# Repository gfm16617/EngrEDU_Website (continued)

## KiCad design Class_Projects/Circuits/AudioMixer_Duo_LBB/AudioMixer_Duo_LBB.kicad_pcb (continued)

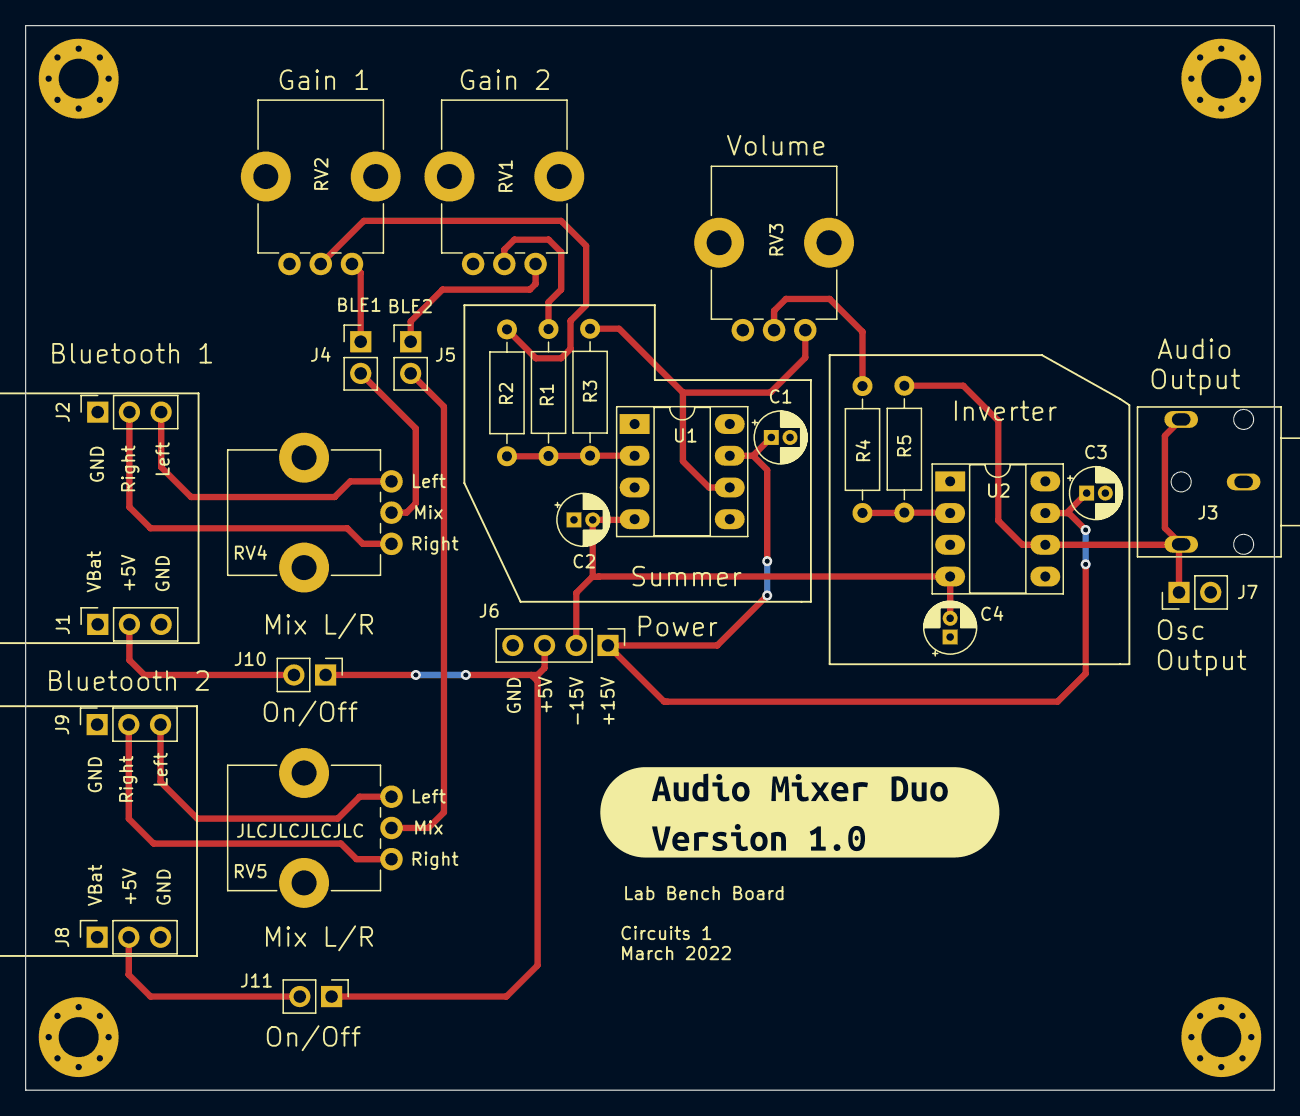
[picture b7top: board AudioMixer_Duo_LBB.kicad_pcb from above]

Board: 2 copper layers, 100.0 x 85.2 mm, 32 parts (0 on the bottom side), 21 nets.

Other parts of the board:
kibuzzard-622CD937: G***; kibuzzard-622CD937

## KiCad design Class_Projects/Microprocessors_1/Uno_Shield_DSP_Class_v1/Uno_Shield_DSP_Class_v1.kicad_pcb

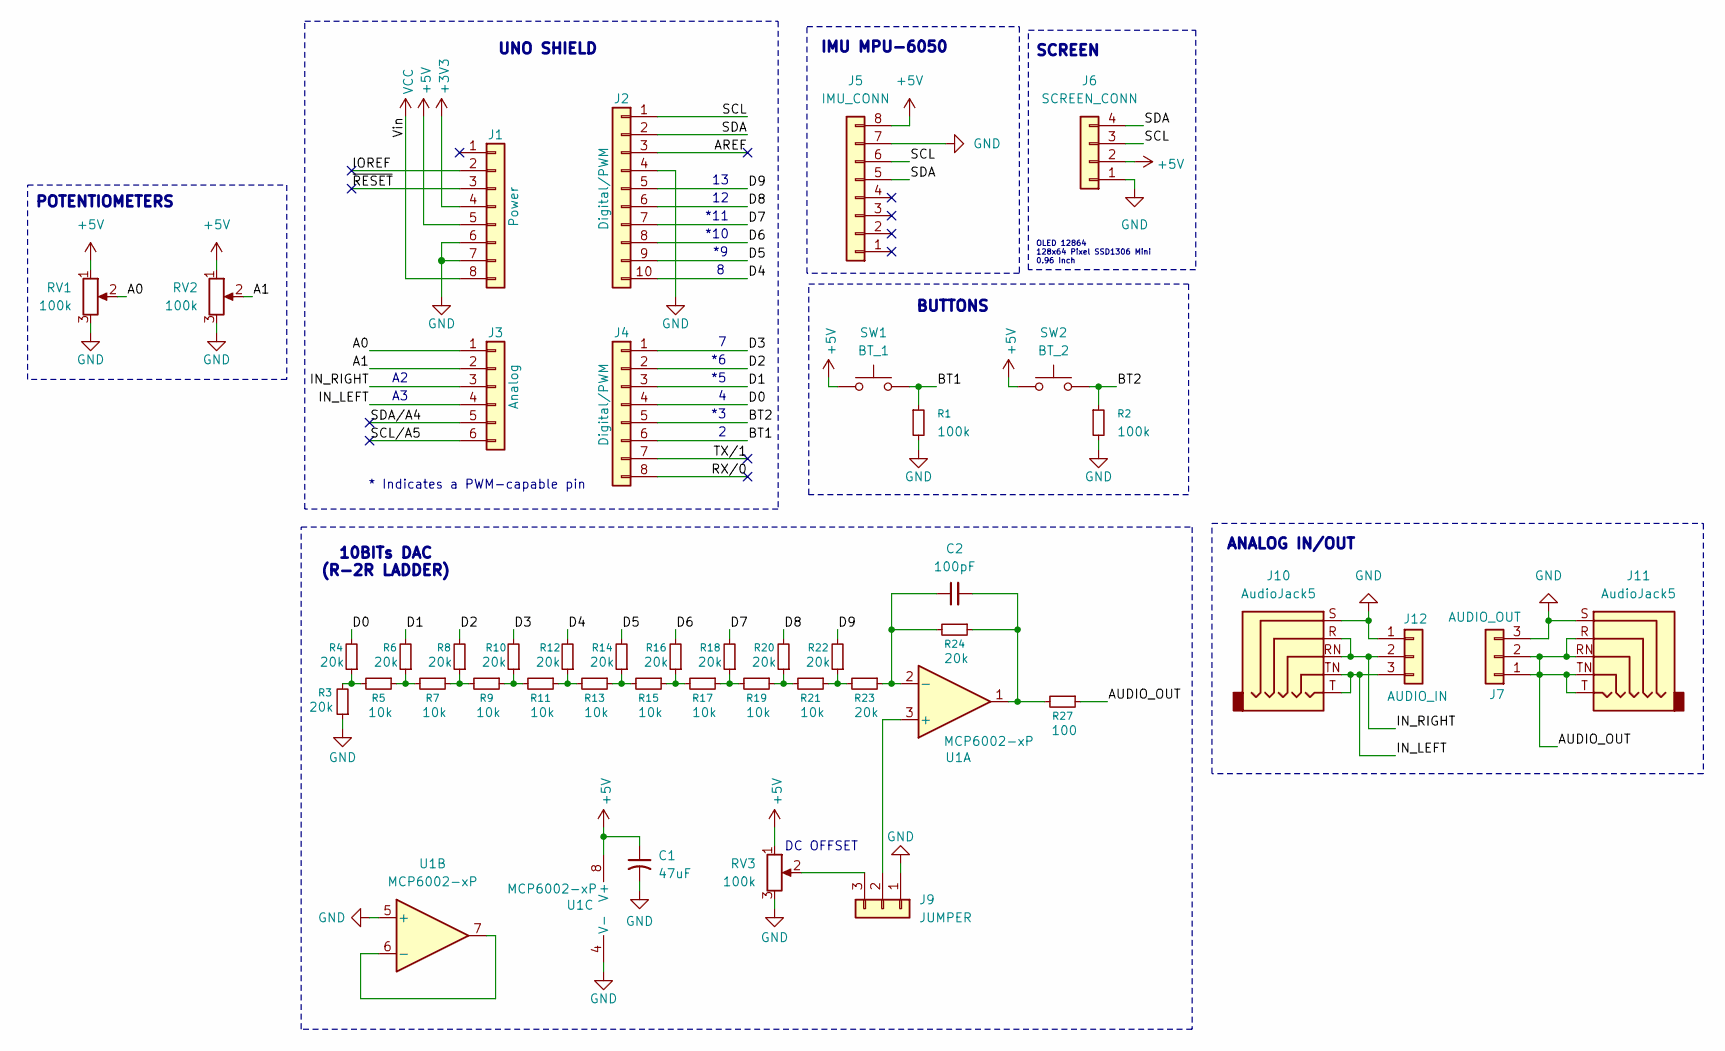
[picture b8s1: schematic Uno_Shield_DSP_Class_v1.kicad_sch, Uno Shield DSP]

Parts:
C1: 47uF; CP_Radial_D6.3mm_P2.50mm
C2: 100pF; C_Disc_D5.0mm_W2.5mm_P2.50mm
J1: Power; PinSocket_1x08_P2.54mm_Vertical
J2: Digital/PWM; PinSocket_1x10_P2.54mm_Vertical
J3: Analog; PinSocket_1x06_P2.54mm_Vertical
J4: Digital/PWM; PinSocket_1x08_P2.54mm_Vertical
J5: IMU_CONN; PinSocket_1x08_P2.54mm_Vertical
J6: SCREEN_CONN; PinHeader_1x04_P2.54mm_Vertical
J7: AUDIO_OUT; PinHeader_1x03_P2.54mm_Vertical
J9: JUMPER; PinHeader_1x03_P2.54mm_Vertical
J10, J11: AudioJack5; Jack_3.5mm_CUI_SJ1-3525N_Horizontal
J12: AUDIO_IN; PinHeader_1x03_P2.54mm_Vertical
R1, R2: 100k; R_Axial_DIN0309_L9.0mm_D3.2mm_P2.54mm_Vertical
R3, R4, R6, R8, R10, R12, R14, R16, R18, R20, R22, R23, R24: 20k; R_Axial_DIN0309_L9.0mm_D3.2mm_P2.54mm_Vertical
R5, R7, R9, R11, R13, R15, R17, R19, R21: 10k; R_Axial_DIN0309_L9.0mm_D3.2mm_P2.54mm_Vertical
R27: 100; R_Axial_DIN0309_L9.0mm_D3.2mm_P2.54mm_Vertical
RV1, RV2, RV3: 100k; Potentiometer_Bourns_3386P_Vertical
SW1: BT_1; SW_PUSH_6mm
SW2: BT_2; SW_PUSH_6mm
U1: MCP6002-xP; DIP-8_W7.62mm_Socket_LongPads

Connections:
+3V3: J1.4
+5V: C1.1, J1.5, J5.8, J6.2, RV1.1, RV2.1, RV3.1, SW1.1, SW2.1, U1.8 (V+)
/A0: J3.1, RV1.2
/A1: J3.2, RV2.2
/AREF: J2.3
/AUDIO_OUT: J7.1, J7.2, J11.R, J11.RN, J11.T, J11.TN, R27.1
/BT1: J4.6, R1.1, SW1.2
/BT2: J4.5, R2.1, SW2.2
/D0: J4.4, R4.2
/D1: J4.3, R6.2
/D2: J4.2, R8.2
/D3: J4.1, R10.2
/D4: J2.10, R12.2
/D5: J2.9, R14.2
/D6: J2.8, R16.2
/D7: J2.7, R18.2
/D8: J2.6, R20.2
/D9: J2.5, R22.2
/IN_LEFT: J3.4, J10.T, J10.TN, J12.3
/IN_RIGHT: J3.3, J10.R, J10.RN, J12.2
/IOREF: J1.2
/RX/0: J4.8
/SCL: J2.1, J5.6, J6.3
/SCL/A5: J3.6
/SDA: J2.2, J5.5, J6.4
/SDA/A4: J3.5
/TX/1: J4.7
/~RESET: J1.3
GND: C1.2, J1.6, J1.7, J2.4, J5.7, J6.1, J7.3, J9.1, J10.S, J11.S, J12.1, R1.2, R2.2, R3.1, RV1.3, RV2.3, RV3.3, U1.4 (V-), U1.5 (+)
unnamed: C2.2, R24.1, R27.2, U1.1
unnamed: J9.2, U1.3 (+)
unnamed: J9.3, RV3.2
unnamed: R3.2, R4.1, R5.2
unnamed: R5.1, R6.1, R7.2
unnamed: R7.1, R8.1, R9.2
unnamed: R9.1, R10.1, R11.2
unnamed: R11.1, R12.1, R13.2
unnamed: R13.1, R14.1, R15.2
unnamed: R15.1, R16.1, R17.2
unnamed: R17.1, R18.1, R19.2
unnamed: R19.1, R20.1, R21.2
unnamed: R21.1, R22.1, R23.2
unnamed: C2.1, R23.1, R24.2, U1.2 (-)
unnamed: U1.6 (-), U1.7
VCC: J1.8

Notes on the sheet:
BUTTONS
IMU MPU-6050
POTENTIOMETERS
*11
DC OFFSET
10BITs DAC (R-2R LADDER)
ANALOG IN/OUT
*10
OLED 12864 128x64 Pixel SSD1306 Mini 0.96 Inch
* Indicates a PWM-capable pin
SCREEN
UNO SHIELD

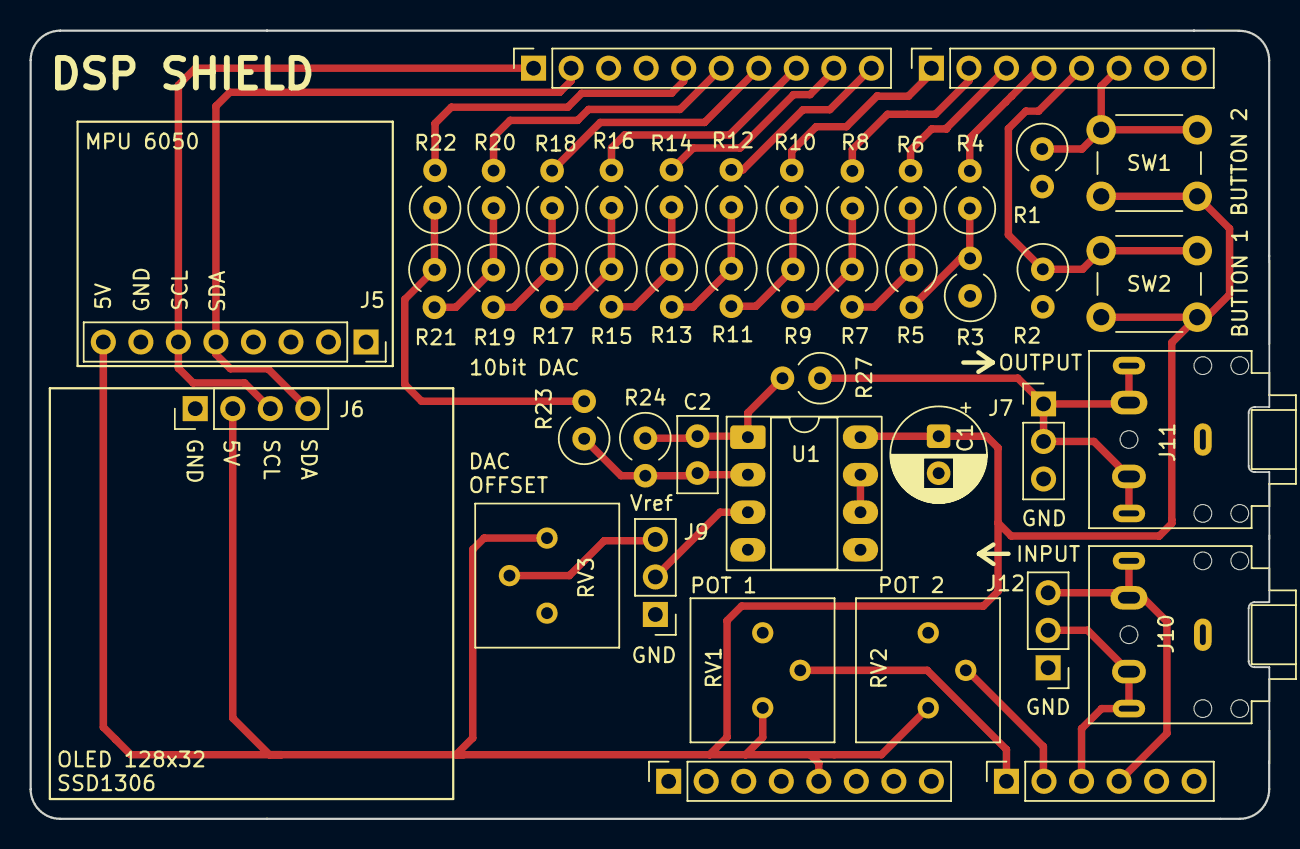
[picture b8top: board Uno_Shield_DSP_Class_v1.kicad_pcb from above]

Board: 2 copper layers, 83.8 x 53.3 mm, 44 parts (0 on the bottom side), 36 nets.

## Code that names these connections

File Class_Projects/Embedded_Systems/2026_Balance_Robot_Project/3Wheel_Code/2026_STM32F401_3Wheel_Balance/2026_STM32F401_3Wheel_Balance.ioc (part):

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Mcu.Name=STM32F401R(B-C)Tx
Mcu.Package=LQFP64
Mcu.UserName=STM32F401RBTx
PA0-WKUP.Signal=S_TIM5_CH1
PA1.Signal=S_TIM2_CH2
PA10.Mode=Asynchronous
PA10.Signal=USART1_RX
PA11.Mode=Device_Only
PA11.Signal=USB_OTG_FS_DM
PA12.Mode=Device_Only
PA12.Signal=USB_OTG_FS_DP
PA13.Mode=Serial_Wire
PA13.Signal=SYS_JTMS-SWDIO
PA14.Mode=Serial_Wire
PA14.Signal=SYS_JTCK-SWCLK
PA2.GPIOParameters=GPIO_Label
PA2.GPIO_Label=AIN2
PA2.Signal=GPIO_Output
PA3.GPIOParameters=GPIO_Label
PA3.GPIO_Label=AIN1
PA3.Signal=GPIO_Output
PA4.GPIOParameters=GPIO_Label
PA4.GPIO_Label=STANDBY
PA4.Signal=GPIO_Output
PA5.Signal=S_TIM2_CH1_ETR
PA6.GPIOParameters=GPIO_Label
PA6.GPIO_Label=BIN1
PA6.Signal=GPIO_Output
PA7.GPIOParameters=GPIO_Label
PA7.GPIO_Label=BIN2
PA7.Signal=GPIO_Output
PA8.Mode=I2C
PA8.Signal=I2C3_SCL
PA9.Mode=Asynchronous
PA9.Signal=USART1_TX
PB1.GPIOParameters=GPIO_Label
PB1.GPIO_Label=USER_LED
PB1.Signal=GPIO_Output
PB6.Signal=S_TIM4_CH1
PB7.Signal=S_TIM4_CH2
PB8.Mode=I2C
PB8.Signal=I2C1_SCL
PB9.Mode=I2C
PB9.Signal=I2C1_SDA
PC13-ANTI_TAMP.GPIOParameters=GPIO_Label
PC13-ANTI_TAMP.GPIO_Label=IMU_INT
PC13-ANTI_TAMP.Signal=GPIO_Input
PC6.Signal=S_TIM3_CH1
PC9.Mode=I2C
PC9.Signal=I2C3_SDA
PH0\ -\ OSC_IN.Mode=HSE-External-Oscillator
PH0\ -\ OSC_IN.Signal=RCC_OSC_IN
PH1\ -\ OSC_OUT.Mode=HSE-External-Oscillator
PH1\ -\ OSC_OUT.Signal=RCC_OSC_OUT
RCC.HSE_VALUE=16000000
RCC.SYSCLKFreq_VALUE=84000000
RCC.SYSCLKSource=RCC_SYSCLKSOURCE_PLLCLK
board=custom

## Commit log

2022-05-20 LTSpice Variable Parameter
2022-05-20 Example 1 .op simulation
2022-05-20 Example 1 simulation transient with multiple parameters
2022-05-21 Variable Parameter Maximum Power Transfer
2022-05-21 Example 2
2022-05-21 Variable Resistor and Potentiometer Files
2022-05-21 Potentiometer Example
2022-05-21 External Libraries
2022-05-21 Example 1 DC
2022-05-22 Dependent Sources Examples
2022-05-22 Depende Sources Remove Files
2022-05-22 New Dependent Source Files
2022-05-22 New Files added
2022-05-22 Switches Examples
2022-05-22 RLC Added
2022-05-22 example deleted
2022-05-22 new example 2 file
2022-05-26 Okika LP Test
2022-05-27 File updated
2022-05-27 New okika file 16Mhz
2022-05-27 Pi ahf file
2022-05-27 Option 1 FPAA code
2022-05-27 FPAA Arduino Uno Project
2022-05-27 FPAA Dynamic Reconfiguration
2022-05-27 FPAA Starter Board PCB
2022-06-08 Phasor Circuits
2022-06-08 Fourier Series Articles
2022-11-14 FFT Article
2022-11-14 Another guitar distortion pedal
2022-11-21 gnuradio intro examples
2022-11-21 NI DAQ fist example
2022-11-29 gnuradio projects fundamentals
2022-11-29 gnuradio freq domain real vs complex
2022-11-29 gnuradio freq linearity
2022-11-29 gnuradio convolution
2022-11-30 gnuradio iq transmitter
2022-11-30 folder removed
2022-11-30 gnuradio constellations
2022-11-30 gnuradio am modulation
2022-11-30 gnuradio am voice example
2022-11-30 gnuradio am ssb
2022-11-30 product demodulator fix
2022-12-02 gnuradio frequency direction
2022-12-02 gnuradio fm modulation
2022-12-05 ook modulation (ask)
2022-12-05 m-ary ask modulation
2022-12-06 fsk modulation examples
2022-12-07 bfsk modulation
2022-12-08 PSK modulation examples
2022-12-08 new qpsk module
2022-12-08 rrc_pulse_shapes
2022-12-09 BPSK and QPSK gnuradio examples
2022-12-09 QAM gnuradio flowgraph
2022-12-09 ni daq info code
2022-12-09 remove old folder
2023-02-24 ni daq ai single demand
2023-02-24 remove file
2023-02-24 ni daq single demand matplotlib and pyqtgraph
2023-02-27 ni daq on demand gui
2023-03-05 ni daq single finite
2023-03-06 ni single ai continuous
2023-03-07 simple FM Radio
2023-03-09 version 2
2023-03-23 PCB Tutorial Board March 2023
2023-03-23 arduino code
2023-03-23 remove folder
2023-03-23 PCB Tutorial Kitchen Timer (March 2023)
2023-03-23 gerber zip file
2023-03-26 new code
2023-03-26 new files
2023-04-05 new version of the code with comments according to mutex standards
2023-04-05 Phase B
2023-04-06 alirugdlfghdflkgjdahgka
2023-04-06 gdsagdsa
2023-04-06 Clock version 2.2
2023-04-23 ATMEGA dev board files
2023-06-07 arduino code timers CTC
2023-06-07 new timer version
2023-06-08 timer 2 ctc example
2023-07-22 new documents about visa and scpi
2023-07-22 python code examples
2023-07-31 python code example that shows the different ways to acquire data from the NI DAQ
2023-08-01 bad code removed
2023-08-01 MCP4251 simple test
2023-09-26 electric vlsi icon article
2024-02-08 up1 class arduino code for shield
2024-02-08 comment a line of code
2024-02-08 removed extra file
2024-05-26 final project PCB schedule for embedded systems class
2024-05-26 DDS Shield PCB Design Files
2024-05-26 pcb components
2024-05-26 unzip these components here
2024-05-26 stm32f dds code
2024-05-26 some code for now
2024-05-26 dds stm32f405 pcb design
2024-05-26 components
2024-05-26 unzip here
2024-05-28 stm32cubeide project
2024-05-28 main.c deleted
2024-05-31 new board version
2024-06-01 schematics fixed
2024-06-07 UART FTDI PCB KiCad Project
2024-06-08 FTDI 3D Support
2024-06-26 ECG KiCad projects
2024-06-27 charge pump kicad project
2024-06-30 RP2040
2024-07-16 fixes
2024-09-06 RP2040 Kicad 8.0 Project
2024-10-30 Project 15 - EngrEDU
2024-11-23 codde for the STM32C011J
2024-11-24 I2C resistor addded to the PCB
2024-11-24 STM32C011J IMU Test
2024-11-25 ADS8689 PCB Board
2024-11-25 ADS8689 PCB and Arduino Code
2024-11-25 removed initial project ADS8689
2024-12-22 STM32F303 Teensy Shape
2024-12-22 STM32F303 ST32CubeIDE Project
2025-02-02 Project 18
2025-02-13 old version
2025-02-13 new version
2025-05-21 Brush EBoot Version 1
2025-07-07 test run
2025-09-06 fgpa articles first file
2025-09-08 blinkled Quartus Project
2025-09-23 ultrasonic sensor code
2025-10-19 example
2025-10-19 kicad project
2025-10-19 removed
2025-10-19 board
2025-10-19 audio board test
2025-10-19 board test
2025-12-04 levitation project test
2025-12-04 wrl board
2026-01-04 PCbCupid Example
2026-01-04 folder deleted
2026-02-14 microprocessors 1 2026 project
2026-02-15 gerber
2026-03-11 audio mixer done in 2022 for circuits 1
2026-03-11 audio mixer duo for circuits 1 class 2022
2026-03-11 firmware code to interact with AD2 serial
2026-03-15 OTC231 firmware code to program the FPAA using AD2 software
2026-03-16 code for state driven example with ESP32 and OTC231
2026-03-17 algorithm method example for ESP32
2026-03-17 OTC231 algorithm example
2026-03-17 okika articles test with github and wordpress
2026-03-17 mkdocs build
2026-03-18 okika articles removed
2026-03-20 ESP32 webserver example
2026-04-03 2026 stm32 blink project
2026-04-03 python for engineers installation files
2026-04-16 test
2026-04-16 deleted
2026-04-17 HC-SR04 project solution
2026-04-19 eurorack module done in 2020, documentation revised
2026-05-01 new projects added to the repository. 2026 Embedded System Project 2026 Daisy Seed POD Board
2026-05-22 added new wrl files into daisy pod
2026-06-01 3Wheel code and CAD files added
2026-06-01 stm32cube code uploaded for the 3wheel version
2026-06-14 added files for Okika standalone single AN231 chip with protoboard
2026-06-21 ESP32 and FPAA Analoguino
2026-06-21 firmware code uploaded
2026-06-24 add random python file
2026-06-25 OTC code added
2026-06-25 new OTC2312 bypass
2026-06-29 OTC2312 State Driven example
2026-06-30 2026_ESP32_FPAA_v3 added with Analog pins on ESP32 fixed
2026-06-30 Delete Okika/2026_ESP32_FPAA_v2 directory
    no longer needed
